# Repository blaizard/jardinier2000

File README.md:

# Jardinier 2000

# Getting started

To initialize and deploy the server, simply run:
```bash
./app.py update
./app.py init
./app.py start prod
```

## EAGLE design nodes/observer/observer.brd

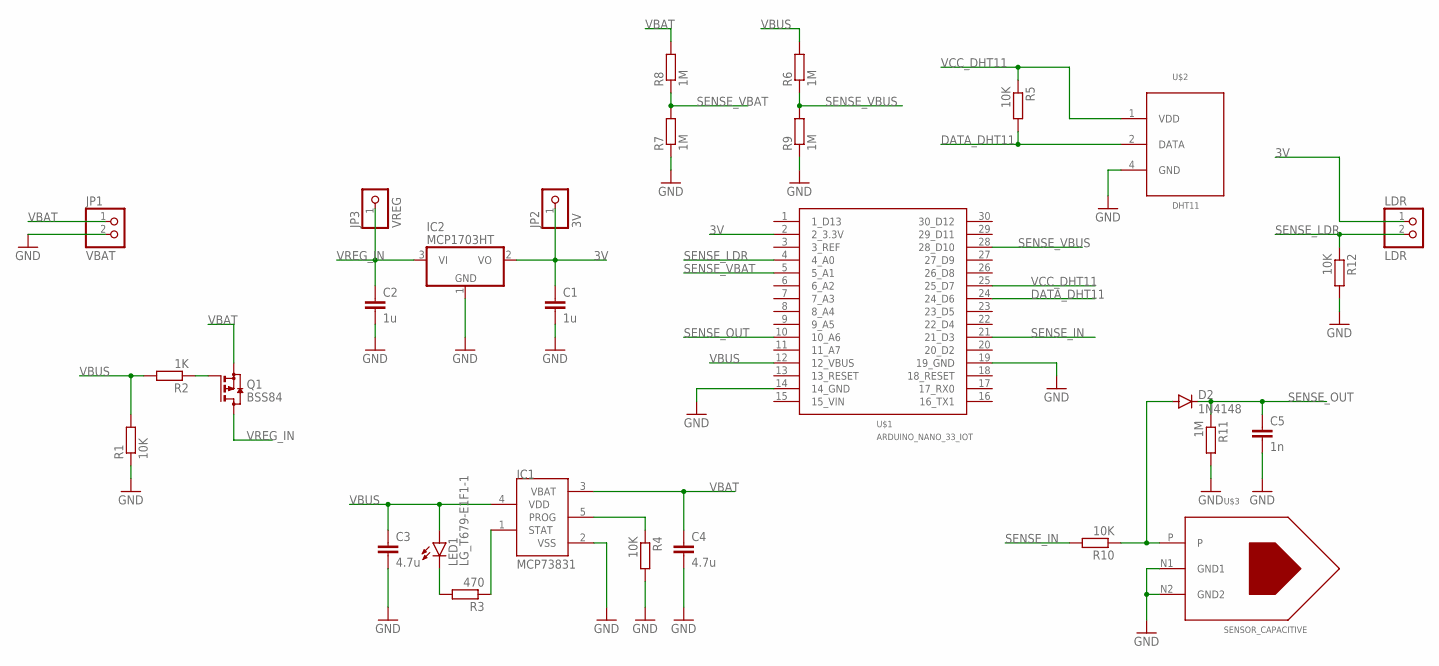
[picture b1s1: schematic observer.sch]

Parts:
C1, C2: 1u; C0805
C3, C4: 4.7u; C0805
C5: 1n; C0805
D2: 1N4148; MICROMELF-W
IC1: MCP73831; SOT23-5L
IC2: MCP1703HT; SOT23
JP1: VBAT; 1X02
JP2: 3V; 1X01
JP3: VREG; 1X01
LDR: LDR; 1X02
LED1: LG_T679-E1F1-1; PLCC2
Q1: BSS84; SOT23
R1, R4, R5, R10, R12: 10K; R0805
R2: 1K; R0805
R3: 470; R0805
R6, R7, R8, R9, R11: 1M; R0805
U$1: ARDUINO_NANO_33_IOT
U$2: DHT11
U$3: SENSOR_CAPACITIVE; SENSOR_CAPACITIVE_MOISTURE

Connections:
3V: C1.1, IC2.2 (VO), JP2.1, LDR.1, U$1.2 (2_3.3V)
DATA_DHT11: R5.2, U$1.24 (24_D6), U$2.2 (DATA)
GND: C1.2, C2.2, C3.2, C4.2, C5.2, IC1.2 (VSS), IC2.1 (GND), JP1.2, R1.1, R4.2, R7.1, R9.1, R11.2, R12.2, U$1.14 (14_GND), U$1.19 (19_GND), U$2.4 (GND), U$3.N1 (GND1), U$3.N2 (GND2)
unnamed: Q1.1 (G), R2.1
unnamed: LED1.C, R3.2
unnamed: IC1.1 (STAT), R3.1
unnamed: IC1.5 (PROG), R4.1
unnamed: D2.A, R10.1, U$3.P
SENSE_IN: R10.2, U$1.21 (21_D3)
SENSE_LDR: LDR.2, R12.1, U$1.4 (4_A0)
SENSE_OUT: C5.1, D2.C, R11.1, U$1.10 (10_A6)
SENSE_VBAT: R7.2, R8.1, U$1.5 (5_A1)
SENSE_VBUS: R6.1, R9.2, U$1.28 (28_D10)
VBAT: C4.1, IC1.3 (VBAT), JP1.1, Q1.2 (S), R8.2
VBUS: C3.1, IC1.4 (VDD), LED1.A, R1.2, R2.2, R6.2, U$1.12 (12_VBUS)
VCC_DHT11: R5.1, U$1.25 (25_D7), U$2.1 (VDD)
VREG_IN: C2.1, IC2.3 (VI), JP3.1, Q1.3 (D)

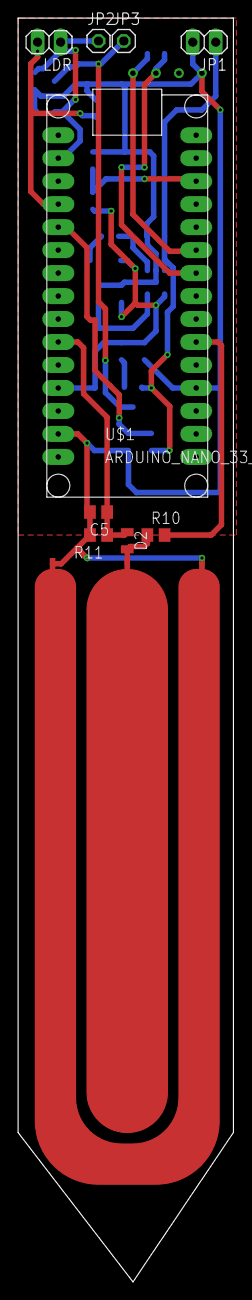
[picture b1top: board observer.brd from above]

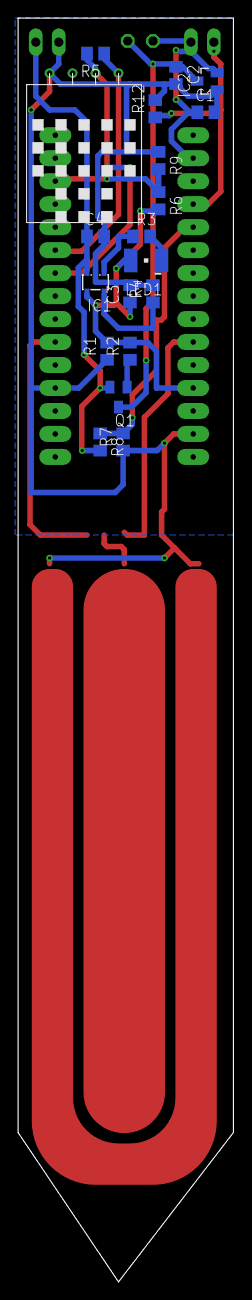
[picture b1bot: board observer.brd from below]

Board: 2 copper layers, 23.8 x 139.7 mm, 29 parts (19 on the bottom side), 17 nets.

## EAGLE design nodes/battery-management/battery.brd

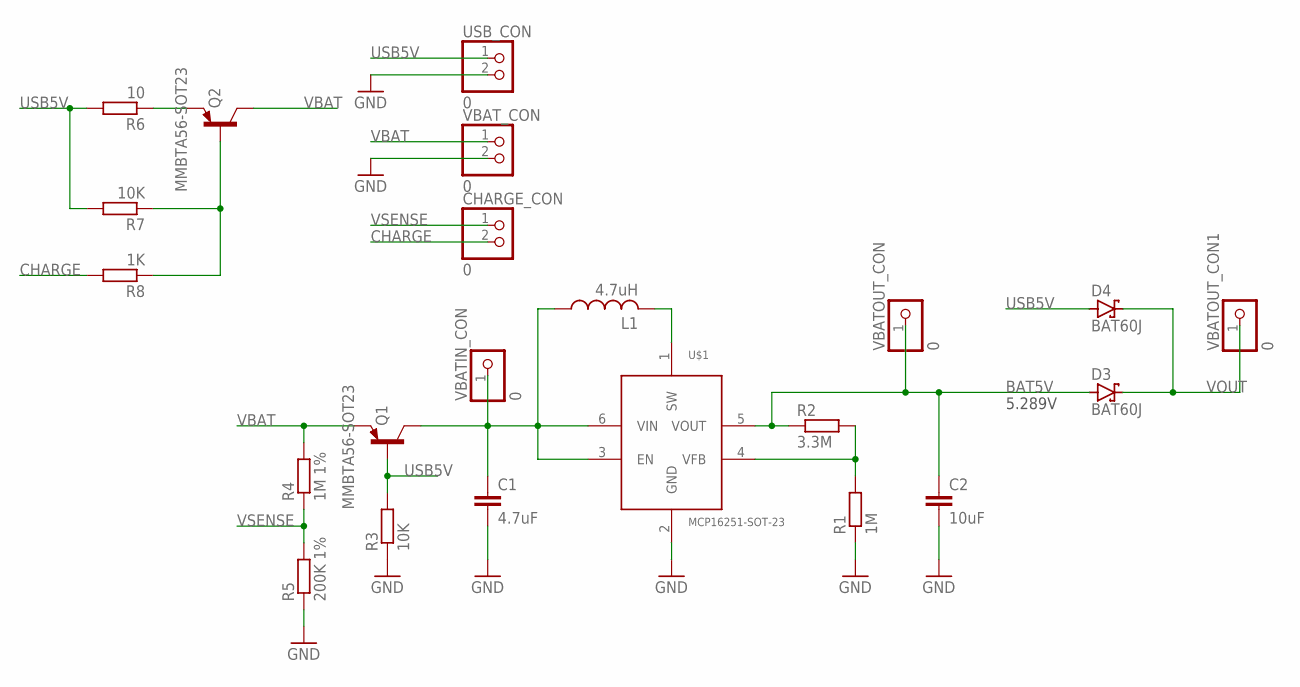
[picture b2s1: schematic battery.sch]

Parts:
C1: 4.7uF; C0805
C2: 10uF; C0805
CHARGE_CON: 0; 1X02
D3, D4: BAT60J; SOD323_ST
L1: 4.7uH; L4532P
Q1, Q2: MMBTA56-SOT23; SOT23
R1: 1M; R0805
R2: 3.3M; R0805
R3, R7: 10K; R0805
R4: 1M 1%; R0805
R5: 200K 1%; R0805
R6: 10; R0805
R8: 1K; R0805
U$1: MCP16251-SOT-23; SOT-23
USB_CON: 0; 1X02
VBATIN_CON: 0; 1X01
VBATOUT_CON, VBATOUT_CON1: 0; 1X01
VBAT_CON: 0; 1X02

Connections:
BAT5V: C2.1, D3.A, R2.1, U$1.5 (VOUT), VBATOUT_CON.1
CHARGE: CHARGE_CON.2, R8.2
GND: C1.2, C2.2, R1.1, R3.1, R5.1, U$1.2 (GND), USB_CON.2, VBAT_CON.2
unnamed: L1.2, U$1.1 (SW)
unnamed: R1.2, R2.2, U$1.4 (VFB)
unnamed: Q2.1 (B), R7.1, R8.1
unnamed: Q2.2 (E), R6.1
unnamed: C1.1, L1.1, Q1.3 (C), U$1.3 (EN), U$1.6 (VIN), VBATIN_CON.1
USB5V: D4.A, Q1.1 (B), R3.2, R6.2, R7.2, USB_CON.1
VBAT: Q1.2 (E), Q2.3 (C), R4.2, VBAT_CON.1
VOUT: D3.C, D4.C, VBATOUT_CON1.1
VSENSE: CHARGE_CON.1, R4.1, R5.2

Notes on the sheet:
5.289V

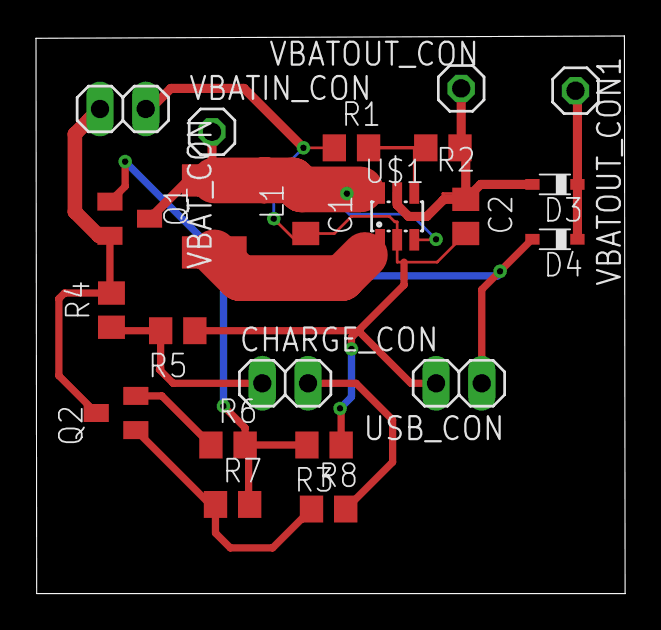
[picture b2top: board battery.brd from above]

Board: 2 copper layers, 32.7 x 31.0 mm, 22 parts (0 on the bottom side), 12 nets.

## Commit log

2019-08-04 Implementation of timeseries (wip)
2019-08-05 Adding chart
2019-08-06 Adding spline
2019-08-06 Adding config.json
2019-08-06 Use token instead of key
2019-08-08 Adding arduino node
2019-08-11 Cleanup
2019-08-12 Fixed timeout issue
2019-08-12 Updated lib
2019-08-13 Adding moisture and luminosity sensors
2019-08-13 Adding sensor title
2019-08-13 Set the view to 1 full day
2019-08-25 Adding battery management
2019-08-26 Rearange application structure
2019-08-26 Adding string
2019-08-27 Only send data via Wifi every 2 hours
2019-08-28 Begining of water provider scad design
2019-12-02 Making new board
2019-12-14 Workign version
2019-12-15 Adding batteryCC
